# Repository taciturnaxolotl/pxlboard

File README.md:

# PxlBoard

## BOM

| Part                           | Quantity             | Price  | LCSC                                                                                                                                                                     | Notes                                                                    |
| ------------------------------ | -------------------- | ------ | ------------------------------------------------------------------------------------------------------------------------------------------------------------------------ | ------------------------------------------------------------------------ |
| PCB (OSHPark)                  | 1                    | $47.25 |                                                                                                                                                                          | Purple PCB; Most expensive manufacturer but also looks gorgeous          |
| PCB (JLCPCB)                   | 1                    | $24.82 |                                                                                                                                                                          | Custom PCB - Green; Mid-range price                                      |
| PCB (PCBWay)                   | 1                    | $12.80 |                                                                                                                                                                          | Custom PCB - Various colors; Most affordable option (kinda suprisingly?) |
| Seeed XIAO RP2040              | 1                    | $3.99  | [Seeed Studio](https://www.seeedstudio.com/XIAO-RP2040-v1-0-p-5026.html)                                                                                                 | Brain of the operation                                                   |
| SK6812 LEDs                    | 65                   | $6.40  | [C5380879](https://www.lcsc.com/product-detail/RGB-LEDs-Built-in-IC_OPSCO-Optoelectronics-SKC6812RGBW-WS-B_C5380879.html?s_z=n_rgbw)                                     | RGB addressable LEDs; $0.0985 each, forms the 8x8 grid                   |
| LIS3DHTR Accelerometer         | 1                    | $0.60  | [C15134](https://www.lcsc.com/product-detail/Accelerometers_STMicroelectronics-LIS3DHTR_C15134.html?s_z=n_LIS3DHTR)                                                      | 3-axis accelerometer; same as the one used on the spark tilt jam         |
| Capacitor 100nF - ceramic      | 20 (min size) need 1 | $0.29  | [C24497](https://www.lcsc.com/product-detail/Multilayer-Ceramic-Capacitors-MLCC-SMD-SMT_Samsung-Electro-Mechanics-CL31B104KBCNNNC_C24497.html?s_z=n_1206%2520100nf)      | 1206 package                                                             |
| Capacitor 10uF - ceramic       | 10 (min size) need 9 | $0.34  | [C13585](https://www.lcsc.com/product-detail/Multilayer-Ceramic-Capacitors-MLCC-SMD-SMT_Samsung-Electro-Mechanics-CL31A106KBHNNNE_C13585.html?s_z=n_10uf%25201206)       | 1206 package                                                             |
| Capacitor 10nf - ceramic       | 20 (min size) need 1 | $0.23  | [C1846](https://www.lcsc.com/product-detail/Multilayer-Ceramic-Capacitors-MLCC-SMD-SMT_FH-Guangdong-Fenghua-Advanced-Tech-1206B103K500NT_C1846.html?s_z=n_10nf%25201206) | 1206 package                                                             |
| Capacitor 100uF - electrolytic | 5 (min size) need 1  | $0.87  | [C1954161](https://www.lcsc.com/product-detail/Tantalum-Capacitors_Vishay-Intertech-TMCMA0J107MTRF_C1954161.html?s_z=n_100uf)                                            | 1206 package                                                             |
| Capacitor 470uF - polymer      | 5 (min size) need 1  | $0.59  | [C41410213](https://www.lcsc.com/product-detail/Polymer-Aluminum-Capacitors_Yunxing-SPT1AM471E09TRVZC_C41410213.html?s_z=n_470uf%252010v%2520polymer)                    | 10V 470uF Polymer ±20% SMD,D6.3xL9mm Polymer Aluminum Capacitors ROHS    |
| USB-c connector                | 5 (min size) need 1  | $0.87  | [C165948](https://www.lcsc.com/product-detail/C165948.html)                                                                                                              | 5A 1 16P Female Type-C SMD USB Connectors ROHS                           |

Total (with pcbway): ~$28.25

## Schematics

> If you want an iteractive version use [`kicanvas`](https://kicanvas.org/?github=https%3A%2F%2Fgithub.com%2Ftaciturnaxolotl%2Fpxlboard%2Fblob%2Fmain%2Fkicad%2Fpxlboard.kicad_pro)!

<div align="center">

</div>

### Pinout

#### XIAO RP2040 Connections

| XIAO Pin       | Connected To           | Description    |
| -------------- | ---------------------- | -------------- |
| D0/GPIO26/A0   | -                      | Unused         |
| D1/GPIO27/A1   | -                      | Unused         |
| D2/GPIO28/A2   | -                      | Unused         |
| D3/GPIO29/A3   | -                      | Unused         |
| D4/GPIO6/SDA   | LIS3DHTR SDA           | I2C Data Line  |
| D5/GPIO7/SCL   | LIS3DHTR SCL           | I2C Clock Line |
| D6/GPIO0/TX    | -                      | Unused         |
| D7/GPIO1/RX    | NEOPIXEL_SIG           | LED Data In    |
| D8/GPIO2/SCK   | -                      | Unused         |
| D9/GPIO4/MISO  | -                      | Unused         |
| D10/GPIO3/MOSI | -                      | Unused         |
| 3V3            | LIS3DHTR VDD_IO        | 3.3V Power     |
| GND            | LIS3DHTR GND, LEDs GND | Ground         |
| 5V             | LEDs VDD               | 5V Power       |

#### LIS3DHTR Accelerometer

| LIS3DHTR Pin | Connected To | Description          |
| ------------ | ------------ | -------------------- |
| VDD          | 3.3V         | Power Supply         |
| VDD_IO       | 3.3V         | Interface Power      |
| GND          | GND          | Ground               |
| SDA          | XIAO D4      | I2C Data             |
| SCL          | XIAO D5      | I2C Clock            |
| INT1         | -            | Interrupt (not used) |
| INT2         | -            | Interrupt (not used) |

<p align="center">
	<i><code>&copy 2025-present <a href="https://github.com/taciturnaxolotl">Kieran Klukas</a></code></i>
</p>

<p align="center">
	
</p>

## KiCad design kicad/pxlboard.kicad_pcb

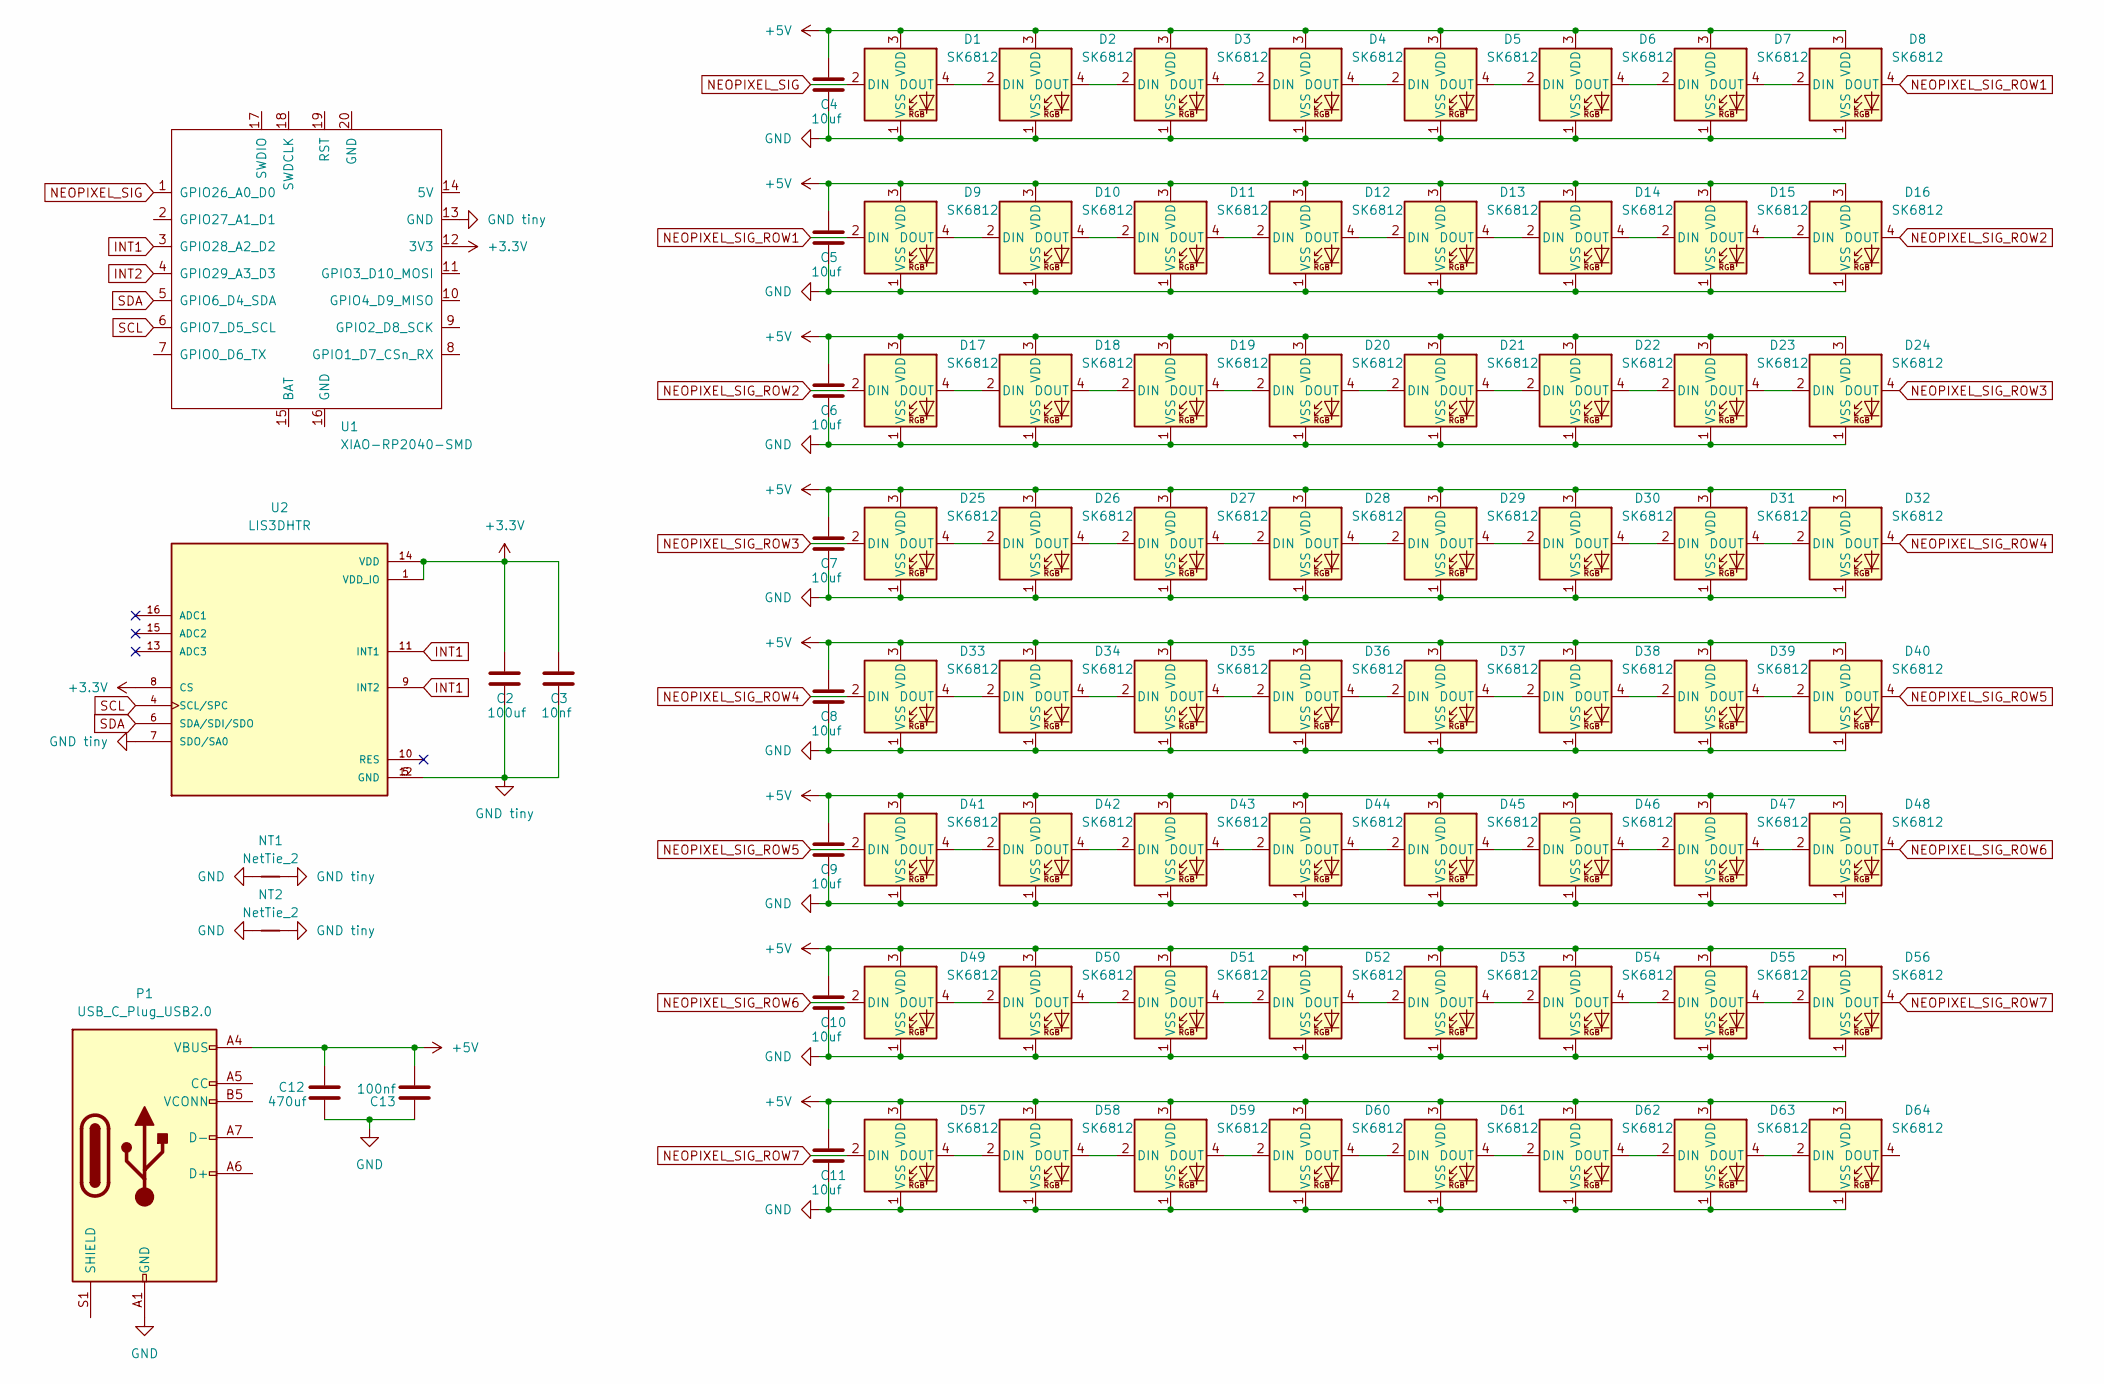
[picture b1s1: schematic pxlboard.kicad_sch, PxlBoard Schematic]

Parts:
C2: 100uf; C_1206_3216Metric_Pad1.33x1.80mm_HandSolder
C3: 10nf; C_1206_3216Metric_Pad1.33x1.80mm_HandSolder
C4, C5, C6, C7, C8, C9, C10, C11: 10uf; C_1206_3216Metric_Pad1.33x1.80mm_HandSolder
C12: 470uf; CP_Elec_6.3x9.9
C13: 100nf; C_1206_3216Metric_Pad1.33x1.80mm_HandSolder
D1, D2, D3, D4, D5, D6, D7, D8, D9, D10, D11, D12, D13, D14, D15, D16, D17, D18, D19, D20, D21, D22, D23, D24, D25, D26, D27, D28, D29, D30, D31, D32, D33, D34, D35, D36, D37, D38, D39, D40, D41, D42, D43, D44, D45, D46, D47, D48, D49, D50, D51, D52, D53, D54, D55, D56, D57, D58, D59, D60, D61, D62, D63, D64: SK6812; LED_SK6812_PLCC4_5.0x5.0mm_P3.2mm
NT1, NT2: NetTie_2; NetTie-2_SMD_Pad0.5mm
P1: USB_C_Plug_USB2.0; TYPE-C-31-M-12
U1: XIAO-RP2040-SMD
U2: LIS3DHTR; XDCR_LIS3DHTR; PARTREV 2; DigiKey_Part_Number 497-10613-2-ND

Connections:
+3.3V: C2.1, C3.1, U1.12 (3V3), U2.1 (VDD_IO), U2.8 (CS), U2.14 (VDD)
+5V: C4.1, C5.1, C6.1, C7.1, C8.1, C9.1, C10.1, C11.1, C12.1, C13.2, D1.3 (VDD), D2.3 (VDD), D3.3 (VDD), D4.3 (VDD), D5.3 (VDD), D6.3 (VDD), D7.3 (VDD), D8.3 (VDD), D9.3 (VDD), D10.3 (VDD), D11.3 (VDD), D12.3 (VDD), D13.3 (VDD), D14.3 (VDD), D15.3 (VDD), D16.3 (VDD), D17.3 (VDD), D18.3 (VDD), D19.3 (VDD), D20.3 (VDD), D21.3 (VDD), D22.3 (VDD), D23.3 (VDD), D24.3 (VDD), D25.3 (VDD), D26.3 (VDD), D27.3 (VDD), D28.3 (VDD), D29.3 (VDD), D30.3 (VDD), D31.3 (VDD), D32.3 (VDD), D33.3 (VDD), D34.3 (VDD), D35.3 (VDD), D36.3 (VDD), D37.3 (VDD), D38.3 (VDD), D39.3 (VDD), D40.3 (VDD), D41.3 (VDD), D42.3 (VDD), D43.3 (VDD), D44.3 (VDD), D45.3 (VDD), D46.3 (VDD), D47.3 (VDD), D48.3 (VDD), D49.3 (VDD), D50.3 (VDD), D51.3 (VDD), D52.3 (VDD), D53.3 (VDD), D54.3 (VDD), D55.3 (VDD), D56.3 (VDD), D57.3 (VDD), D58.3 (VDD), D59.3 (VDD), D60.3 (VDD), D61.3 (VDD), D62.3 (VDD), D63.3 (VDD), D64.3 (VDD), P1.A4 (VBUS), P1.A9 (VBUS), P1.B4 (VBUS), P1.B9 (VBUS)
GND: C4.2, C5.2, C6.2, C7.2, C8.2, C9.2, C10.2, C11.2, C12.2, C13.1, D1.1 (VSS), D2.1 (VSS), D3.1 (VSS), D4.1 (VSS), D5.1 (VSS), D6.1 (VSS), D7.1 (VSS), D8.1 (VSS), D9.1 (VSS), D10.1 (VSS), D11.1 (VSS), D12.1 (VSS), D13.1 (VSS), D14.1 (VSS), D15.1 (VSS), D16.1 (VSS), D17.1 (VSS), D18.1 (VSS), D19.1 (VSS), D20.1 (VSS), D21.1 (VSS), D22.1 (VSS), D23.1 (VSS), D24.1 (VSS), D25.1 (VSS), D26.1 (VSS), D27.1 (VSS), D28.1 (VSS), D29.1 (VSS), D30.1 (VSS), D31.1 (VSS), D32.1 (VSS), D33.1 (VSS), D34.1 (VSS), D35.1 (VSS), D36.1 (VSS), D37.1 (VSS), D38.1 (VSS), D39.1 (VSS), D40.1 (VSS), D41.1 (VSS), D42.1 (VSS), D43.1 (VSS), D44.1 (VSS), D45.1 (VSS), D46.1 (VSS), D47.1 (VSS), D48.1 (VSS), D49.1 (VSS), D50.1 (VSS), D51.1 (VSS), D52.1 (VSS), D53.1 (VSS), D54.1 (VSS), D55.1 (VSS), D56.1 (VSS), D57.1 (VSS), D58.1 (VSS), D59.1 (VSS), D60.1 (VSS), D61.1 (VSS), D62.1 (VSS), D63.1 (VSS), D64.1 (VSS), NT1.1, NT2.1, P1.A1 (GND), P1.A12 (GND), P1.B1 (GND), P1.B12 (GND)
GND tiny: C2.2, C3.2, NT1.2, NT2.2, U1.13 (GND), U2.5 (GND), U2.7 (SDO/SA0), U2.12 (GND)
INT1: U1.3 (GPIO28_A2_D2), U2.9 (INT2), U2.11 (INT1)
INT2: U1.4 (GPIO29_A3_D3)
NEOPIXEL_SIG: D1.2 (DIN), U1.1 (GPIO26_A0_D0)
NEOPIXEL_SIG_ROW1: D8.4 (DOUT), D9.2 (DIN)
NEOPIXEL_SIG_ROW2: D16.4 (DOUT), D17.2 (DIN)
NEOPIXEL_SIG_ROW3: D24.4 (DOUT), D25.2 (DIN)
NEOPIXEL_SIG_ROW4: D32.4 (DOUT), D33.2 (DIN)
NEOPIXEL_SIG_ROW5: D40.4 (DOUT), D41.2 (DIN)
NEOPIXEL_SIG_ROW6: D48.4 (DOUT), D49.2 (DIN)
NEOPIXEL_SIG_ROW7: D56.4 (DOUT), D57.2 (DIN)
unnamed: D1.4 (DOUT), D2.2 (DIN)
unnamed: D2.4 (DOUT), D3.2 (DIN)
unnamed: D3.4 (DOUT), D4.2 (DIN)
unnamed: D4.4 (DOUT), D5.2 (DIN)
unnamed: D5.4 (DOUT), D6.2 (DIN)
unnamed: D6.4 (DOUT), D7.2 (DIN)
unnamed: D7.4 (DOUT), D8.2 (DIN)
unnamed: D9.4 (DOUT), D10.2 (DIN)
unnamed: D10.4 (DOUT), D11.2 (DIN)
unnamed: D11.4 (DOUT), D12.2 (DIN)
unnamed: D12.4 (DOUT), D13.2 (DIN)
unnamed: D13.4 (DOUT), D14.2 (DIN)
unnamed: D14.4 (DOUT), D15.2 (DIN)
unnamed: D15.4 (DOUT), D16.2 (DIN)
unnamed: D17.4 (DOUT), D18.2 (DIN)
unnamed: D18.4 (DOUT), D19.2 (DIN)
unnamed: D19.4 (DOUT), D20.2 (DIN)
unnamed: D20.4 (DOUT), D21.2 (DIN)
unnamed: D21.4 (DOUT), D22.2 (DIN)
unnamed: D22.4 (DOUT), D23.2 (DIN)
unnamed: D23.4 (DOUT), D24.2 (DIN)
unnamed: D25.4 (DOUT), D26.2 (DIN)
unnamed: D26.4 (DOUT), D27.2 (DIN)
unnamed: D27.4 (DOUT), D28.2 (DIN)
unnamed: D28.4 (DOUT), D29.2 (DIN)
unnamed: D29.4 (DOUT), D30.2 (DIN)
unnamed: D30.4 (DOUT), D31.2 (DIN)
unnamed: D31.4 (DOUT), D32.2 (DIN)
unnamed: D33.4 (DOUT), D34.2 (DIN)
unnamed: D34.4 (DOUT), D35.2 (DIN)
unnamed: D35.4 (DOUT), D36.2 (DIN)
unnamed: D36.4 (DOUT), D37.2 (DIN)
unnamed: D37.4 (DOUT), D38.2 (DIN)
unnamed: D38.4 (DOUT), D39.2 (DIN)
unnamed: D39.4 (DOUT), D40.2 (DIN)
unnamed: D41.4 (DOUT), D42.2 (DIN)
unnamed: D42.4 (DOUT), D43.2 (DIN)
unnamed: D43.4 (DOUT), D44.2 (DIN)
unnamed: D44.4 (DOUT), D45.2 (DIN)
unnamed: D45.4 (DOUT), D46.2 (DIN)
unnamed: D46.4 (DOUT), D47.2 (DIN)
unnamed: D47.4 (DOUT), D48.2 (DIN)
unnamed: D49.4 (DOUT), D50.2 (DIN)
unnamed: D50.4 (DOUT), D51.2 (DIN)
unnamed: D51.4 (DOUT), D52.2 (DIN)
unnamed: D52.4 (DOUT), D53.2 (DIN)
unnamed: D53.4 (DOUT), D54.2 (DIN)
unnamed: D54.4 (DOUT), D55.2 (DIN)
unnamed: D55.4 (DOUT), D56.2 (DIN)
unnamed: D57.4 (DOUT), D58.2 (DIN)
unnamed: D58.4 (DOUT), D59.2 (DIN)
unnamed: D59.4 (DOUT), D60.2 (DIN)
unnamed: D60.4 (DOUT), D61.2 (DIN)
unnamed: D61.4 (DOUT), D62.2 (DIN)
unnamed: D62.4 (DOUT), D63.2 (DIN)
unnamed: D63.4 (DOUT), D64.2 (DIN)
SCL: U1.6 (GPIO7_D5_SCL), U2.4 (SCL/SPC)
SDA: U1.5 (GPIO6_D4_SDA), U2.6 (SDA/SDI/SDO)

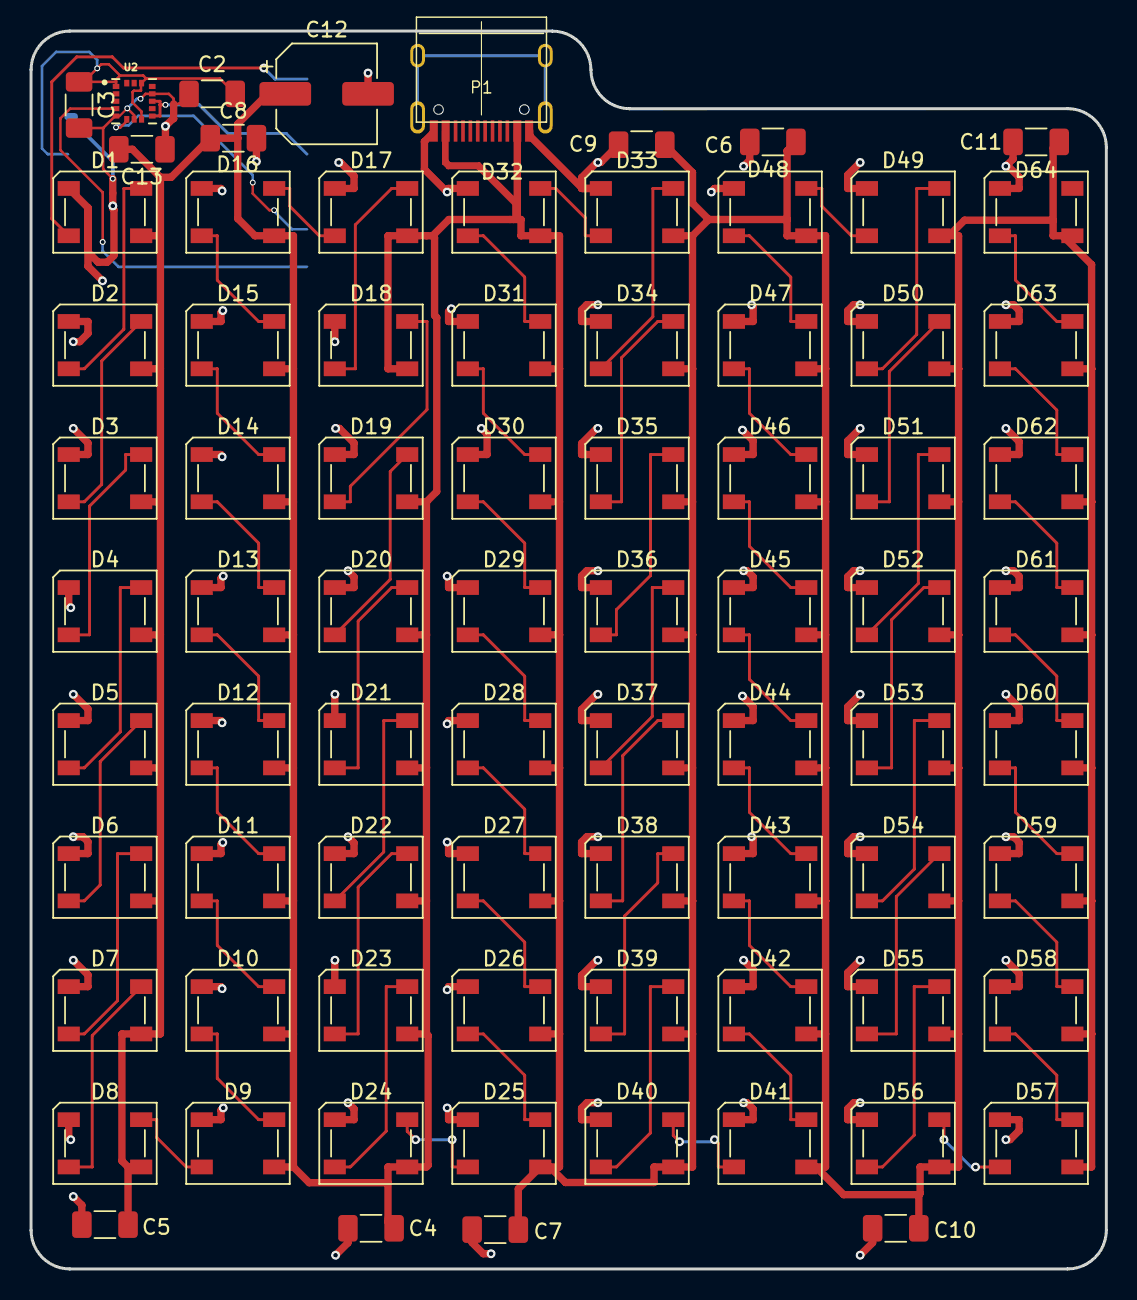
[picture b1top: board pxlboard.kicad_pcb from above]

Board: 2 copper layers, 72.8 x 83.8 mm, 81 parts (1 on the bottom side), 71 nets.

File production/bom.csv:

Comment,Designator,Footprint,LCSC,Quantity
XIAO-RP2040-SMD,U1,XIAO-RP2040-SMD,N/A,1
SK6812,"D39,D31,D18,D37,D28,D21,D5,D3,D44,D24,D63,D52,D42,D56,D4,D43,D49,D60,D53,D62,D40,D50,D20,D41,D8,D30,D10,D58,D57,D33,D25,D16,D17,D23,D46,D59,D64,D27,D61,D7,D12,D19,D14,D36,D48,D54,D45,D55,D2,D29,D34,D35,D47,D1,D6,D26,D15,D38,D51,D9,D13,D22,D11,D32",LED_SK6812_PLCC4_5.0x5.0mm_P3.2mm,C5380879,64
LIS3DHTR,U2,XDCR_LIS3DHTR,C15134,1
100nF,C13,C_1206_3216Metric_Pad1.33x1.80mm_HandSolder,C24497,1
10uF,"C11,C4,C5,C10,C9,C8,C7,C6",C_1206_3216Metric_Pad1.33x1.80mm_HandSolder,C13585,8
470uF,C12,CP_Elec_6.3x9.9,C41410213,1
100uF,C2,C_1206_3216Metric_Pad1.33x1.80mm_HandSolder,C1954161,1
10nF,C3,C_1206_3216Metric_Pad1.33x1.80mm_HandSolder,C1846,1

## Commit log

2025-05-03 docs: add readme and license
2025-05-03 feat: add kicad and schematic
2025-05-03 feat: add basic matrix
2025-05-03 feat: add accelerometer
2025-05-03 feat: 64 leds and proper trace width
2025-05-03 feat: round off the board
2025-05-03 feat: export for production
2025-05-03 feat: add bom
2025-05-03 docs: add wiring
2025-05-04 docs: update bom
2025-05-04 feat: add caps and reroute
2025-05-04 docs: add schematic and pcb
2025-05-04 docs: add wokwi link
2025-05-04 feat: add production
2025-05-05 feat: round corners
2025-05-05 feat: add power usb c
2025-07-17 docs: add oshpark renders
2025-07-17 [ImgBot] Optimize images
    *Total -- 239.29kb -> 186.69kb (21.98%)
    /.github/images/back.png -- 82.60kb -> 55.18kb (33.19%)
    /.github/images/front.png -- 156.69kb -> 131.51kb (16.07%)
2025-07-17 chore: update oshpark price
2025-08-11 docs: add type c connector to bom
2025-08-12 docs: shuffle readme stuff and add a nice banner
2025-08-12 feat: add oshpark banner
